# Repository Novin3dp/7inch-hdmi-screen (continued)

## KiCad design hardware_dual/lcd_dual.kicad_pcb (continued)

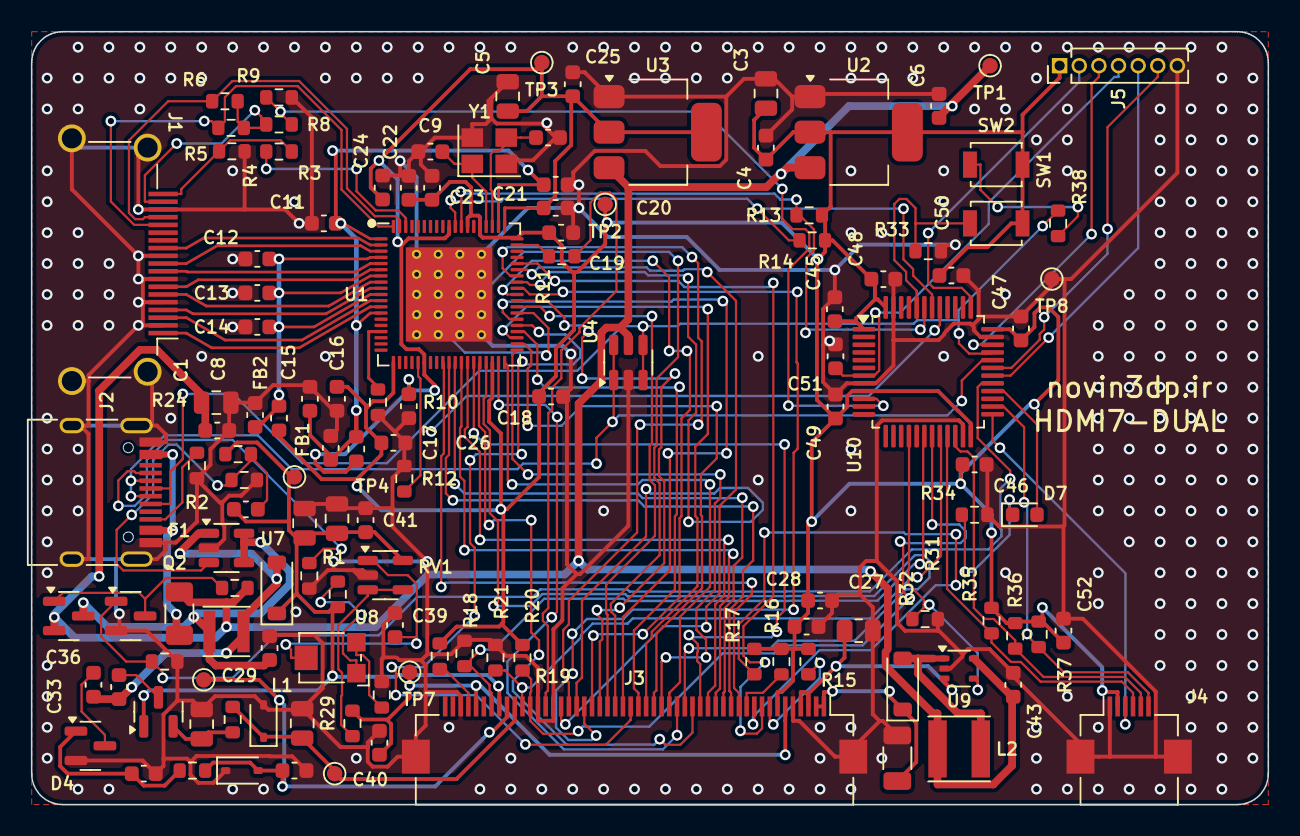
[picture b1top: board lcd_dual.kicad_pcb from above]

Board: 2 copper layers, 80.0 x 50.0 mm, 127 parts (0 on the bottom side), 99 nets.

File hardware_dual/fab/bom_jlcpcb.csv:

Comment,Designator,Footprint,MPN,LCSC Part #,Qty
BOOT (DFU),SW1,SW_SPST_B3U-1000P,Omron B3U-1000P,,1
BOOT CH32,SW2,SW_SPST_B3U-1000P,Omron B3U-1000P,,1
100nF,"C2,C4,C11,C12,C13,C14,C15,C16,C17,C18,C19,C20,C21,C22,C23,C24,C28,C39,C41,C45,C46,C47,C48,C49,C51",C_0603_1608Metric,,C14663,25
100nF 50V,"C33,C36",C_0603_1608Metric,,C14663,2
10pF,C30,C_0603_1608Metric,,,1
10uF,"C6,C7,C8,C25,C26,C29,C43",C_0603_1608Metric,,C19702,7
18pF,"C9,C10",C_0603_1608Metric,,,2
1uF,"C27,C40,C52",C_0603_1608Metric,,C15849,3
1uF 25V,"C37,C38",C_0603_1608Metric,,C15849,2
4.7uF,C50,C_0603_1608Metric,,,1
1uF 50V,C34,C_0805_2012Metric,,,1
22uF,"C1,C3,C5",C_0805_2012Metric,,,3
4.7uF 25V,"C31,C32,C35",C_0805_2012Metric,,,3
2.2uF 50V,C42,C_1206_3216Metric,,,1
Touch FPC 6P 0.5mm,J4,Hirose_FH12-6S-0.5SH_1x06-1MP_P0.50mm_Horizontal,Hirose FH12-6S-0.5SH (check contact side of your CTP),,1
HDMI-A receptacle,J1,HDMI_A_Amphenol_10029449-x01xLF_Horizontal,Amphenol 10029449-001RLF (or equivalent SMT HDMI-A),,1
USB-C (power + touch USB),J2,USB_C_Receptacle_HRO_TYPE-C-31-M-12,HRO TYPE-C-31-M-12,C165948,1
25MHz 12pF,Y1,Crystal_SMD_3225-4Pin_3.2x2.5mm,X322525MOB4SI (25MHz CL=12pF),,1
MBR0530,D1,D_SOD-123,MBR0530T1G,,1
MBR0560,D6,D_SOD-123,MBR0560T1G,,1
16V 2%,D3,D_SOD-323,BZX384-B16,,1
6.8V 2%,D5,D_SOD-323,BZX384-B6V8,,1
PTC 1.1A hold,F1,Fuse_1206_3216Metric,1206L110/16 (or BSMD1206-110),,1
600R@100MHz,"FB1,FB2",L_0603_1608Metric,BLM18PG601SN1D,,2
10uH 0.6A,L1,L_Taiyo-Yuden_NR-30xx,NR3015T100M,,1
10uH 1.2A,L2,L_Taiyo-Yuden_NR-40xx,NR4018T100M,,1
green,D7,LED_0603_1608Metric,,,1
STM32F072CBT6 / CH32X035C8T6,U10,LQFP-48_7x7mm_P0.5mm,"STM32F072CBT6 (or CH32X035C8T6, same footprint)",,1
AMS1117-1.8,U3,SOT-223-3_TabPin2,AMS1117-1.8,,1
AMS1117-3.3,U2,SOT-223-3_TabPin2,AMS1117-3.3,C6186,1
2N7002,Q2,SOT-23,2N7002,C8545,1
AO3401A,Q1,SOT-23,AO3401A,C15127,1
BAT54S,"D2,D4",SOT-23,BAT54S,,2
LM321,U8,SOT-23-5,LM321MFX,,1
TPS61040,U7,SOT-23-5,TPS61040DBVR,,1
USBLC6-2SC6,U4,SOT-23-6,USBLC6-2SC6,C7519,1
TPS61169DCKR,U9,SOT-353_SC-70-5,TPS61169DCKR,,1
10k trim (VCOM),RV1,Potentiometer_Bourns_TC33X_Vertical,Bourns TC33X-2-103E,,1
100k,"R4,R22,R23,R32",R_0603_1608Metric,,C25803,4
100k 1%,R25,R_0603_1608Metric,,C25803,1
10k,"R12,R15,R16,R17,R18,R19,R20,R21,R33,R37",R_0603_1608Metric,,C25804,10
13k 1%,R29,R_0603_1608Metric,,,1
1k,"R3,R34",R_0603_1608Metric,,C21190,2
2.2k,"R26,R27,R35,R36",R_0603_1608Metric,,,4
22R,R11,R_0603_1608Metric,,,1
22k,R8,R_0603_1608Metric,,,1
2k 1%,R10,R_0603_1608Metric,,,1
30k 1%,R28,R_0603_1608Metric,,,1
33R,R30,R_0603_1608Metric,,,1
33k,R9,R_0603_1608Metric,,,1
4.7k,"R13,R14,R38",R_0603_1608Metric,,C23162,3
47k,"R5,R6",R_0603_1608Metric,,,2
5.1k,"R1,R2",R_0603_1608Metric,,C23186,2
750k 1%,R24,R_0603_1608Metric,,,1
1.13R 1%,R31,R_0805_2012Metric,,,1
"AT070TN92 FPC (0.5mm 50P, top contact)",J3,FPC_50P_P0.5_TopContact_AT070TN92,Hirose FH12A-50S-0.5SH(55) (top contact),,1
LT8619C,U1,Lontium_QFN-76_9x9mm_P0.4mm_EP5.81x6.31mm,LT8619C (Lontium),,1

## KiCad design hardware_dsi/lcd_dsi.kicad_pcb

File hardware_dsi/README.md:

# نسخه‌ی DSI: راه‌اندازی AT070TN92 مستقیم از پورت DSI رزبری‌پای

این برد دولایه (۶۸×۴۲ میلی‌متر) همان پنل ۷ اینچ AT070TN92 و تاچ GT915 را این بار از **پورت DSI رزبری‌پای** راه می‌اندازد. نسخه‌ی HDMI در پوشه‌ی `hardware/` دست‌نخورده باقی مانده است.

* **DSI رزبری‌پای** (۲ لِین) ← **ICN6211** (مبدل MIPI-DSI به RGB888) ← کانکتور FPC پنجاه‌پین پنل
* **تاچ GT915** مستقیم روی **I2C کانکتور DSI**؛ درایور `goodix` لینوکس آن را می‌خواند. میکروکنترلر و USB حذف شده‌اند.
* **۵ ولت و ۴ سیگنال کنترلی** با یک کابل ۸ رشته از هدر ۴۰ پین رزبری‌پای می‌آیند (کابل DSI تغذیه‌ی ۵ ولت ندارد).
* بخش تغذیه‌ی پنل (AVDD، VGH، VGL، VCOM) و درایور بک‌لایت همان مدارهای نسخه‌ی HDMI هستند.

> ⚠️ این طراحی همه‌ی بررسی‌های نرم‌افزاری را پاس کرده: DRC، تطبیق شماتیک با PCB و کامپایل Overlay. ولی **هنوز ساخته و روی سخت‌افزار تست نشده است**. بخش «ریسک‌ها» را حتماً بخوانید.

---

## ۱) بلوک دیاگرام

```
 Pi DSI (15P 1mm) ──D0,D1,CLK──► ICN6211 ──RGB888 + DE + PCLK──► J3 (FPC 50P) ──► AT070TN92
        │ SDA/SCL (i2c_csi_dsi)                                     ▲ AVDD/VGH/VGL/VCOM, VLED
        └──────────────────────────► J4 (FPC 6P) ──► تاچ GT915      │
 Pi 40-pin ──J2──► 5V ─► PTC ─► AMS1117-3.3 ─► 3.3V (ICN6211، منطق پنل، تاچ)
                  DSI_EN (GPIO22) ─► EN آی‌سی، RESET پنل (۱ms)، BIAS_EN (RC حدود ۵۰ms) ─► TPS61040 + پمپ‌های بار + LM321
                  TP_INT (GPIO27)، TP_RST (GPIO17) ─► تاچ
                  BL_PWM (GPIO18) ─► TPS61165 (بک‌لایت ۱۸۰mA؛ پیش‌فرض روشن)
```

| بخش | قطعه | توضیح |
|---|---|---|
| مبدل DSI | ICN6211 (QFN48 6×6، LCSC C246085) | هر سه تغذیه 3.3V، کلاک مرجع از کلاک DSI (پایه REF_CLK به زمین)، VCORE با 1µF + 10nF |
| بایاس پنل | TPS61040 + 2×BAT54S + زنر | AVDD 10.4V، VGH 16V، VGL −6.8V |
| VCOM | LM321 + تریمر RV1 | 2.55 تا 4.5 ولت |
| بک‌لایت | TPS61165 | 182mA، روشن/خاموش یا PWM از GPIO18 |
| تغذیه | AMS1117-3.3 | از 5V هدر |

**ترتیب روشن شدن کاملاً سخت‌افزاری است.** وقتی لینوکس پایه‌ی EN پل را بالا می‌برد، RESET پنل بعد از حدود ۱ms آزاد می‌شود. بعد از حدود ۵۰ms هم تغذیه‌های AVDD، VGL و VGH روشن می‌شوند. با خاموش شدن نمایشگر (EN پایین) همه‌ی این‌ها با هم خاموش می‌شوند.

---

## ۲) اتصال به رزبری‌پای

### کابل DSI (J1)

* J1 یک کانکتور FPC پانزده‌پین با گام 1mm است، با همان پین‌اوت کانکتور DSI در Pi 3 و Pi 4.
* **Pi 5 و CM4/CM5** کانکتور ۲۲ پین 0.5mm دارند. برای آن‌ها از کابل استاندارد «Raspberry Pi Display Cable 22-pin to 15-pin» استفاده کنید.
* **جهت کابل:** برای J1 یک کانکتور **Dual-contact** (کنتاکت در بالا و پایین) بگذارید. اگر تصویر نیامد، کابل را در سمت برد **برعکس** (رو به پایین) جا بزنید؛ این کار ترتیب پین‌ها را آینه می‌کند.
* پایه‌های ۱، ۱۴ و ۱۵ کانکتور روی برد عمداً **وصل نیستند**: پین ۱ زمین است و ۱۴ و ۱۵ تغذیه‌ی 3.3V رزبری‌پای. برای همین اگر کابل برعکس جا خورد، 3.3V رزبری‌پای به زمین اتصال کوتاه نمی‌شود. زمین از پایه‌های ۴، ۷، ۱۰ و ۱۳ وصل است.

### کابل هدر (J2، هدر ۸ پین 2.54mm)

| J2 | سیگنال | پین هدر رزبری‌پای |
|---|---|---|
| 1 | +5V | 2 |
| 2 | +5V | 4 |
| 3 | GND | 6 |
| 4 | GND | 9 |
| 5 | DSI_EN (EN آی‌سی ICN6211) | 15 (GPIO22) |
| 6 | TP_INT | 13 (GPIO27) |
| 7 | TP_RST | 11 (GPIO17) |
| 8 | BL_PWM (بک‌لایت) | 12 (GPIO18) |

اگر GPIO دیگری لازم دارید، پارامترهای Overlay را عوض کنید (بخش ۳). بدون سیم BL_PWM بک‌لایت همیشه روشن است (مقاومت pull-up 10k).

### تاچ (J4)

ترتیب پین‌ها مثل نسخه‌ی HDMI است: `1 GND, 2 3.3V, 3 INT, 4 SCL, 5 SDA, 6 RST`. خطوط SCL و SDA به I2C کانکتور DSI وصل‌اند. **ترتیب پین FPC تاچ‌پنل خودتان را چک کنید.**

### مصرف

بک‌لایت حدود 2W، پنل و ICN6211 حدود 0.4W: در مجموع **حدود 0.5A از 5V هدر**. منبع تغذیه‌ی رزبری‌پای باید این جریان اضافه را بدهد (منبع رسمی 3A/5A کافی است).

---

## ۳) نرم‌افزار رزبری‌پای

درایور لینوکس ICN6211 (`chipone-icn6211`) در کرنل اصلی لینوکس هست، **ولی در کرنل Raspberry Pi OS فعال نشده**. اسکریپت `rpi_dsi/icn6211/install.sh` سورس همان نسخه‌ی کرنل را از گیت‌هاب Raspberry Pi دانلود می‌کند. بعد ماژول را می‌سازد و نصب می‌کند، Overlay را کامپایل می‌کند و خط لازم را به `config.txt` اضافه می‌کند:

```sh
sudo apt install linux-headers-rpi-v8 device-tree-compiler   # Pi 5: linux-headers-rpi-2712
cd rpi_dsi/icn6211
sudo ./install.sh
sudo reboot
```

بعد از هر به‌روزرسانی کرنل، `install.sh` را دوباره اجرا کنید.

فایل `rpi_dsi/at070tn92-dsi-overlay.dts` این‌ها را تعریف می‌کند:
* پل `chipone,icn6211` روی DSI1 با ۲ لِین و EN روی GPIO22
* پنل `panel-dpi` با تایمینگ دیتاشیت AT070TN92: 33.3MHz، HFP 210، HBP+HS 46، VFP 22، VBP+VS 23. حالت DE فعال است و داده در لبه‌ی بالارونده‌ی کلاک فرستاده می‌شود، چون پنل در لبه‌ی پایین‌رونده نمونه می‌گیرد.
* بک‌لایت `gpio-backlight` روی GPIO18
* تاچ `goodix` با آدرس 0x5D روی `i2c_csi_dsi`، INT روی GPIO27 و RST روی GPIO17

پارامترهای Overlay (در `config.txt`، مثلاً `dtoverlay=at070tn92-dsi,touch_invx,touch_invy`):

| پارامتر | کار |
|---|---|
| `dsi0` | استفاده از پورت DSI0 (روی Pi 5: DISP0؛ روی CM: DSI0) |
| `enable_gpio=N` / `backlight_gpio=N` / `touch_int=N` / `touch_reset=N` | تغییر GPIOها |
| `touch_invx` / `touch_invy` / `touch_swapxy` | اصلاح جهت تاچ |
| `touch_addr=0x14` / `disable_touch` | آدرس دیگر تاچ / غیرفعال کردن تاچ |
| `clock-frequency=N` | فرکانس پیکسل (پیش‌فرض 33300000) |

چرخش ۱۸۰ درجه: در دسکتاپ از Screen Configuration، یا با سخت‌افزار: R19/R20 (پایه‌های L/R و U/D پنل) را برعکس ببندید و تاچ را با `touch_invx,touch_invy` برگردانید.

---

## ۴) مشخصات PCB

| مورد | مقدار |
|---|---|
| ابعاد | 68 × 42 mm، گوشه‌های گرد R2 (نسخه‌ی HDMI: 80×50) |
| لایه | ۲ لایه، FR4، مس 1oz |
| حداقل ترک/فاصله | 0.15 / 0.15 mm؛ ویا 0.3/0.6 mm (ظرفیت استاندارد JLCPCB) |
| قطعات | ۸۵ قطعه، **فقط روی رو (Top)** |
| زوج‌های DSI | دستی کشیده شده‌اند (حدود ۸ میلی‌متر، ترک 0.2mm). ترتیب لِین‌ها در کانکتور رزبری‌پای و ICN6211 یکی نیست، برای همین زوج کلاک برای عبور از زیر لِین ۱ از لایه‌ی پشت می‌رود (۴ ویا). |
| گذرگاه RGB | ۲۶ خط RGB/DE/DCLK دستی و منظم کشیده شده‌اند: هر خط ستون خودش را دارد و با زاویه‌ی ۳۰ درجه به پد FPC می‌رسد. فقط DE از زیر گذرگاه روی لایه‌ی پشت رد می‌شود. بقیه‌ی نت‌ها با Freerouting کشیده شده‌اند. |
| DRC | **۰ خطا و ۰ اتصال باز**؛ ۸۲ برچسب سیلک بدون تداخل، ۳ برچسب (C40، D3، R18) فقط در نقشه‌ی مونتاژ `docs/img/dsi_pcb_assembly.png` آمده‌اند |

---

## ۵) ساخت (JLCPCB)

1. `hardware_dsi/fab/lcd_dsi_gerbers.zip` برای ساخت PCB.
2. `hardware_dsi/fab/bom_jlcpcb.csv` و `cpl_jlcpcb.csv` برای مونتاژ. شماره‌ی LCSC آی‌سی ICN6211: C246085 (موجودی را هنگام سفارش چک کنید).
3. نقاط تست TP1..TP7 نصب نمی‌شوند. J2 (هدر) را خودتان لحیم کنید.

---

## ۶) ریسک‌ها و نکات (لطفاً بخوانید)

1. **ترتیب رنگ‌ها:** درایور لینوکس رجیستر جابه‌جایی RGB را تنظیم نمی‌کند. طبق راهنمای Chipone فرض شده که حالت پیش‌فرض `DATA[7:0]=R`، `DATA[15:8]=G` و `DATA[23:16]=B` است. اگر قرمز و آبی جابه‌جا بودند، ایراد از این فرض است. می‌توان آن را با یک خط در درایور (رجیستر SYS_CTRL) اصلاح کرد.
2. **جهت کابل DSI** (بخش ۲): کانکتور Dual-contact بگذارید و اگر تصویر نیامد کابل را در سمت برد برعکس کنید.
3. امپدانس زوج‌های DSI روی برد ۲ لایه دقیقاً 100Ω نیست. ولی مسیرها کوتاه‌اند (حدود ۸mm) و سرعت هر لِین برای 800×480 فقط حدود 400Mbps است. ضخامت 1.0mm برای برد بهتر است.
4. پل I2C کانکتور DSI به pull-up نیاز دارد؛ R2/R3 (4.7k به 3.3V برد) روی برد هستند. برد را قبل یا هم‌زمان با رزبری‌پای روشن کنید (هر دو از یک 5V تغذیه می‌شوند).
5. درایور goodix شناسه‌ی GT915 را از خود آی‌سی می‌خواند. Config تاچ‌پنل در فلش GT915 است. اگر محورها برعکس بود از پارامترهای `touch_*` استفاده کنید.
6. VCOM هر پنل را با RV1 برای کمترین فلیکر تنظیم کنید (نقطه‌ی تست TP6).
7. جهت FPC پنل و کانکتور Top-contact مثل نسخه‌ی HDMI است (بخش ۴ README اصلی).

---

## ۷) ساخت دوباره از اسکریپت‌ها

اسکریپت‌های عمومی (`sexpr`، `symlib`، `silk`) از `hardware/gen` استفاده می‌شوند؛ بقیه در `hardware_dsi/gen` هستند و منبع اصلی طراحی فایل `design.py` است.

```sh
cd hardware_dsi/gen
python3 make_libs.py && python3 gen_sch.py && python3 verify_netlist.py
python3.12 pcb.py                         # چیدمان + زوج‌های DSI + خروجی‌های کوتاه پایه‌های ICN6211
python3.12 route.py export
java -jar freerouting-2.0.1.jar --gui.enabled=false -de ../lcd_dsi.dsn -do ../lcd_dsi.ses -mp 100 --router.via_costs=30
python3.12 route.py import ../lcd_dsi.ses
python3.12 check.py --fill
python3 fab.py
```

فایل `lcd_dsi.ses` (مسیرهای برد فعلی) در ریپازیتوری هست.

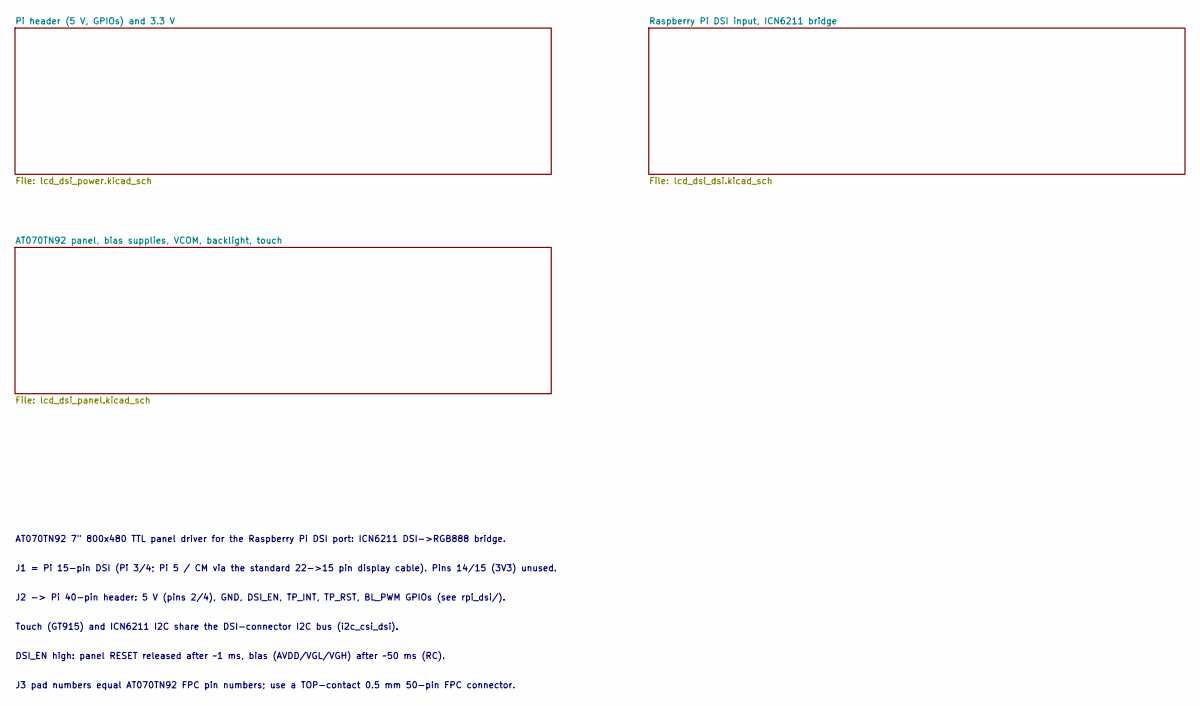
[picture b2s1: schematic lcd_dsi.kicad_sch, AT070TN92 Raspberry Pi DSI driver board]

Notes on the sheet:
AT070TN92 7" 800x480 TTL panel driver for the Raspberry Pi DSI port: ICN6211 DSI->RGB888 bridge.
J1 = Pi 15-pin DSI (Pi 3/4; Pi 5 / CM via the standard 22->15 pin display cable). Pins 14/15 (3V3) unused.
J2 -> Pi 40-pin header: 5 V (pins 2/4), GND, DSI_EN, TP_INT, TP_RST, BL_PWM GPIOs (see rpi_dsi/).
Touch (GT915) and ICN6211 I2C share the DSI-connector I2C bus (i2c_csi_dsi).
DSI_EN high: panel RESET released after ~1 ms, bias (AVDD/VGL/VGH) after ~50 ms (RC).
J3 pad numbers equal AT070TN92 FPC pin numbers; use a TOP-contact 0.5 mm 50-pin FPC connector.

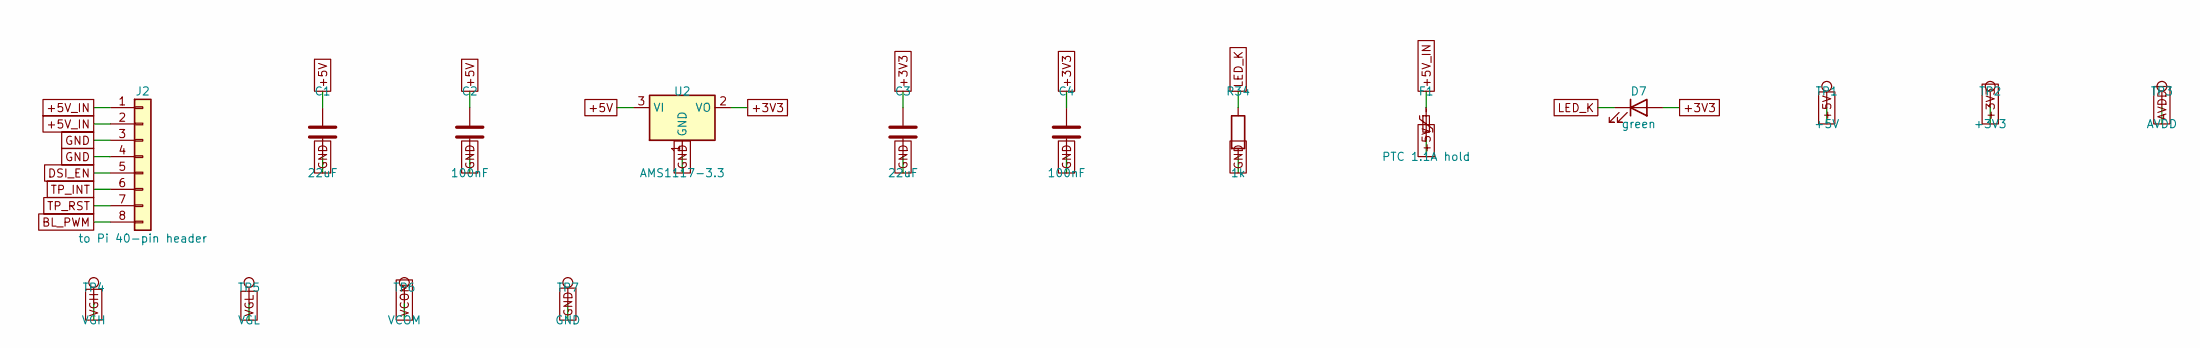
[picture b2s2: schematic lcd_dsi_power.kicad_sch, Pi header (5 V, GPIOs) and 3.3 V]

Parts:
C1, C3: 22uF; C_0805_2012Metric
C2, C4: 100nF; C_0603_1608Metric; LCSC C14663
D7: green; LED_0603_1608Metric
F1: PTC 1.1A hold; Fuse_1206_3216Metric; MPN 1206L110/16 (or BSMD1206-110)
J2: to Pi 40-pin header; PinHeader_1x08_P2.54mm_Vertical; MPN 1x8 2.54mm pin header
R34: 1k; R_0603_1608Metric; LCSC C21190
TP1: +5V; TestPoint_Pad_D1.0mm
TP2: +3V3; TestPoint_Pad_D1.0mm
TP3: AVDD; TestPoint_Pad_D1.0mm
TP4: VGH; TestPoint_Pad_D1.0mm
TP5: VGL; TestPoint_Pad_D1.0mm
TP6: VCOM; TestPoint_Pad_D1.0mm
TP7: GND; TestPoint_Pad_D1.0mm
U2: AMS1117-3.3; SOT-223-3_TabPin2; MPN AMS1117-3.3; LCSC C6186

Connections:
+3V3: C3.1, C4.1, D7.2 (A), TP2.1, U2.2 (VO); also elsewhere on the board
+5V: C1.1, C2.1, F1.2, TP1.1, U2.3 (VI); also elsewhere on the board
+5V_IN: F1.1, J2.1, J2.2
AVDD: TP3.1; also elsewhere on the board
BL_PWM: J2.8; also elsewhere on the board
DSI_EN: J2.5; also elsewhere on the board
GND: C1.2, C2.2, C3.2, C4.2, J2.3, J2.4, R34.2, TP7.1, U2.1 (GND); also elsewhere on the board
LED_K: D7.1 (K), R34.1
TP_INT: J2.6; also elsewhere on the board
TP_RST: J2.7; also elsewhere on the board
VCOM: TP6.1; also elsewhere on the board
VGH: TP4.1; also elsewhere on the board
VGL: TP5.1; also elsewhere on the board

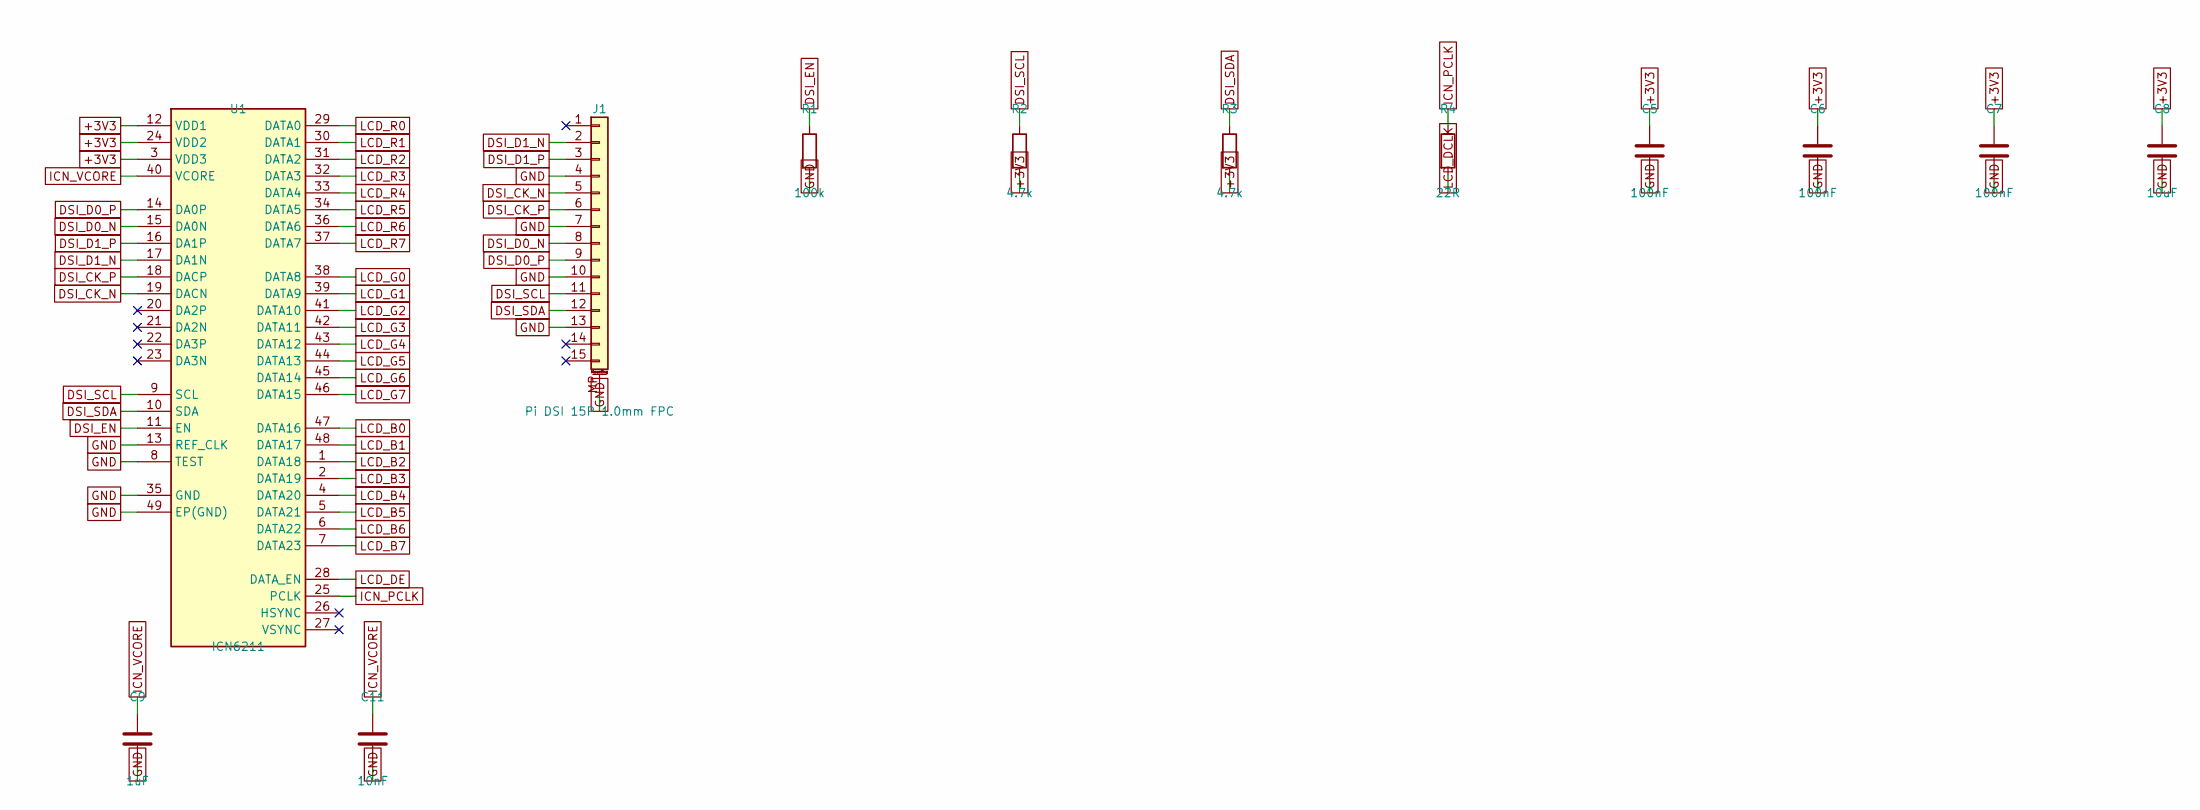
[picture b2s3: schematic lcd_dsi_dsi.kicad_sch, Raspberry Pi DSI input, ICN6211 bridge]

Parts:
C5, C6, C7: 100nF; C_0603_1608Metric; LCSC C14663
C8: 10uF; C_0603_1608Metric; LCSC C19702
C9: 1uF; C_0603_1608Metric; LCSC C15849
C11: 10nF; C_0603_1608Metric
J1: Pi DSI 15P 1.0mm FPC; FPC_15P_P1.0_PiDSI; MPN 1.0mm 15P FPC, dual contact (TE 1-84953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
R1: 100k; R_0603_1608Metric; LCSC C25803
R2, R3: 4.7k; R_0603_1608Metric; LCSC C23162
R4: 22R; R_0603_1608Metric
U1: ICN6211; QFN-48-1EP_6x6mm_P0.4mm_EP4.2x4.2mm_Vias0.3; MPN ICN6211 (Chipone); LCSC C246085

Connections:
+3V3: C5.1, C6.1, C7.1, C8.1, R2.2, R3.2, U1.3 (VDD3), U1.12 (VDD1), U1.24 (VDD2); also elsewhere on the board
DSI_CK_N: J1.5, U1.19 (DACN)
DSI_CK_P: J1.6, U1.18 (DACP)
DSI_D0_N: J1.8, U1.15 (DA0N)
DSI_D0_P: J1.9, U1.14 (DA0P)
DSI_D1_N: J1.2, U1.17 (DA1N)
DSI_D1_P: J1.3, U1.16 (DA1P)
DSI_EN: R1.1, U1.11 (EN); also elsewhere on the board
DSI_SCL: J1.11, R2.1, U1.9 (SCL); also elsewhere on the board
DSI_SDA: J1.12, R3.1, U1.10 (SDA); also elsewhere on the board
GND: C5.2, C6.2, C7.2, C8.2, C9.2, C11.2, J1.4, J1.7, J1.10, J1.13, J1.MP (MountPin), R1.2, U1.8 (TEST), U1.13 (REF_CLK), U1.35 (GND), U1.49 (EP(GND)); also elsewhere on the board
ICN_PCLK: R4.1, U1.25 (PCLK)
ICN_VCORE: C9.1, C11.1, U1.40 (VCORE)
LCD_B0: U1.47 (DATA16); also elsewhere on the board
LCD_B1: U1.48 (DATA17); also elsewhere on the board
LCD_B2: U1.1 (DATA18); also elsewhere on the board
LCD_B3: U1.2 (DATA19); also elsewhere on the board
LCD_B4: U1.4 (DATA20); also elsewhere on the board
LCD_B5: U1.5 (DATA21); also elsewhere on the board
LCD_B6: U1.6 (DATA22); also elsewhere on the board
LCD_B7: U1.7 (DATA23); also elsewhere on the board
LCD_DCLK: R4.2; also elsewhere on the board
LCD_DE: U1.28 (DATA_EN); also elsewhere on the board
LCD_G0: U1.38 (DATA8); also elsewhere on the board
LCD_G1: U1.39 (DATA9); also elsewhere on the board
LCD_G2: U1.41 (DATA10); also elsewhere on the board
LCD_G3: U1.42 (DATA11); also elsewhere on the board
LCD_G4: U1.43 (DATA12); also elsewhere on the board
LCD_G5: U1.44 (DATA13); also elsewhere on the board
LCD_G6: U1.45 (DATA14); also elsewhere on the board
LCD_G7: U1.46 (DATA15); also elsewhere on the board
LCD_R0: U1.29 (DATA0); also elsewhere on the board
LCD_R1: U1.30 (DATA1); also elsewhere on the board
LCD_R2: U1.31 (DATA2); also elsewhere on the board
LCD_R3: U1.32 (DATA3); also elsewhere on the board
LCD_R4: U1.33 (DATA4); also elsewhere on the board
LCD_R5: U1.34 (DATA5); also elsewhere on the board
LCD_R6: U1.36 (DATA6); also elsewhere on the board
LCD_R7: U1.37 (DATA7); also elsewhere on the board

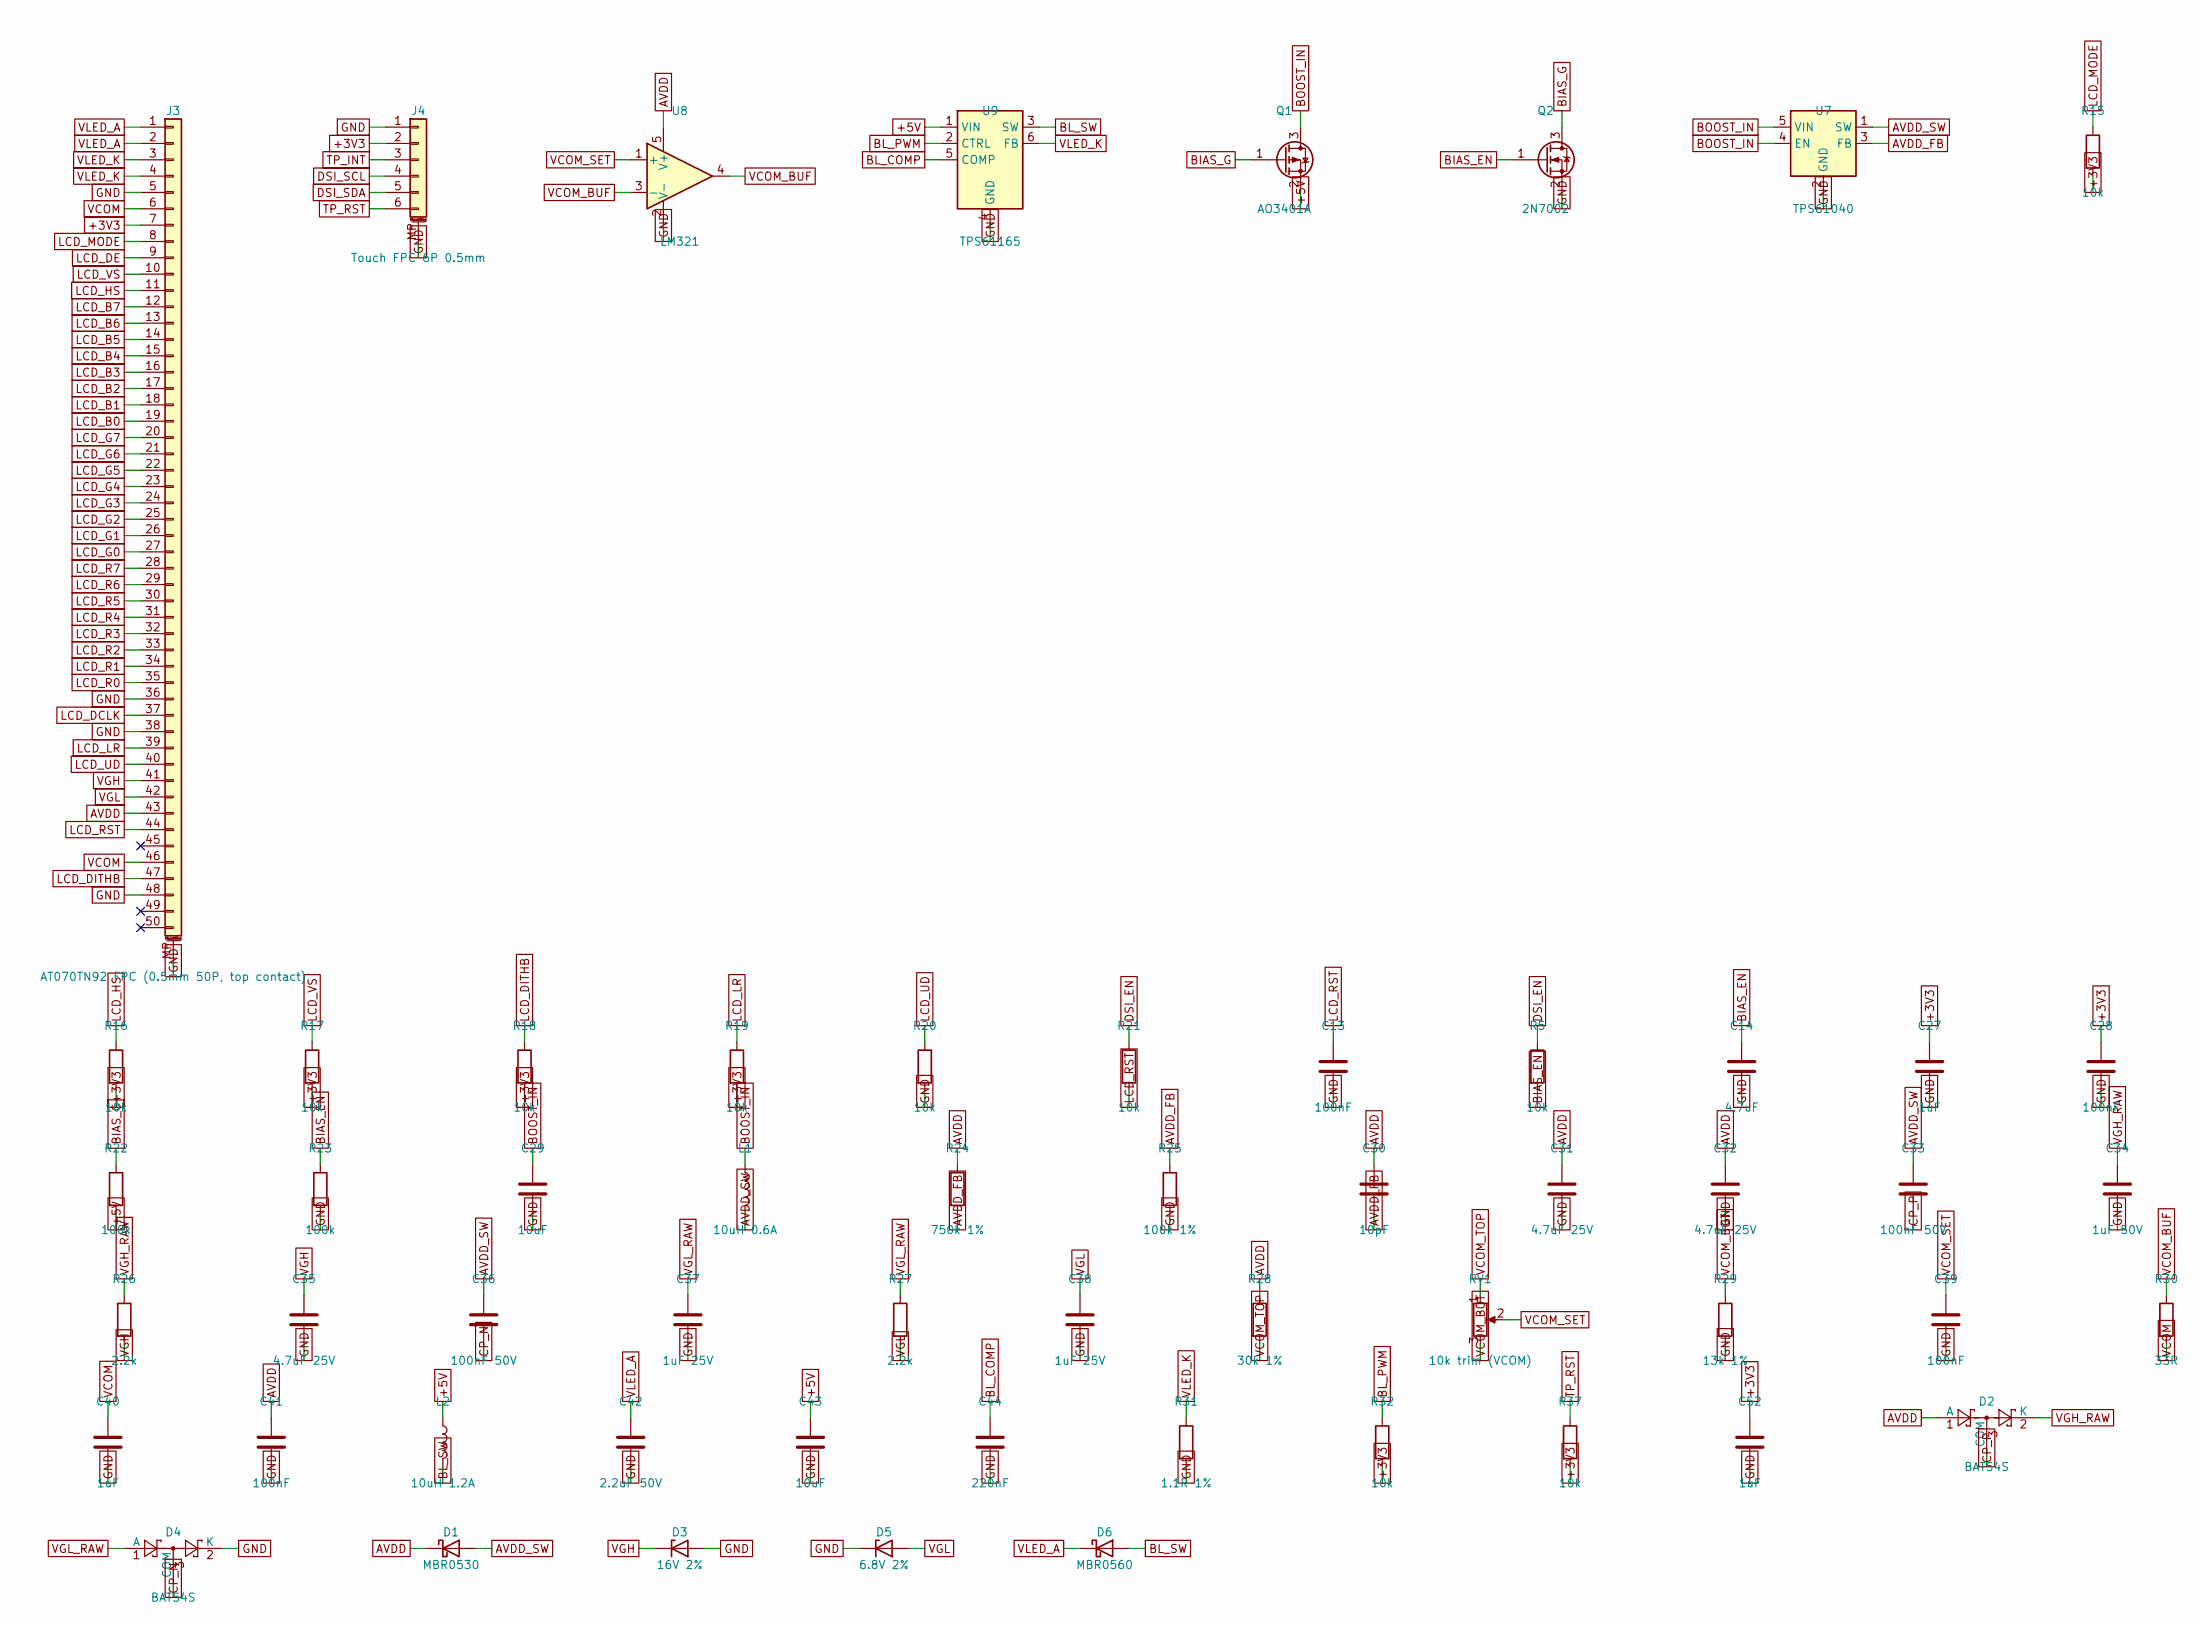
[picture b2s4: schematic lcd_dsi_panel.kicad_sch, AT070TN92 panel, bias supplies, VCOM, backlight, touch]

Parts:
C13, C28, C39, C41: 100nF; C_0603_1608Metric; LCSC C14663
C14: 4.7uF; C_0603_1608Metric
C27, C40, C52: 1uF; C_0603_1608Metric; LCSC C15849
C29, C43: 10uF; C_0603_1608Metric; LCSC C19702
C30: 10pF; C_0603_1608Metric
C31, C32, C35: 4.7uF 25V; C_0805_2012Metric
C33, C36: 100nF 50V; C_0603_1608Metric; LCSC C14663
C34: 1uF 50V; C_0805_2012Metric
C37, C38: 1uF 25V; C_0603_1608Metric; LCSC C15849
C42: 2.2uF 50V; C_1206_3216Metric
C44: 220nF; C_0603_1608Metric
D1: MBR0530; D_SOD-123; MPN MBR0530T1G
D2, D4: BAT54S; SOT-23; MPN BAT54S
D3: 16V 2%; D_SOD-323; MPN BZX384-B16
D5: 6.8V 2%; D_SOD-323; MPN BZX384-B6V8
D6: MBR0560; D_SOD-123; MPN MBR0560T1G
J3: AT070TN92 FPC (0.5mm 50P, top contact); FPC_50P_P0.5_TopContact_AT070TN92; MPN Hirose FH12A-50S-0.5SH(55) (top contact)
J4: Touch FPC 6P 0.5mm; Hirose_FH12-6S-0.5SH_1x06-1MP_P0.50mm_Horizontal; MPN Hirose FH12-6S-0.5SH (check contact sid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
L1: 10uH 0.6A; L_Taiyo-Yuden_NR-30xx; MPN NR3015T100M
L2: 10uH 1.2A; L_Taiyo-Yuden_NR-40xx; MPN NR4018T100M
Q1: AO3401A; SOT-23; MPN AO3401A; LCSC C15127
Q2: 2N7002; SOT-23; MPN 2N7002; LCSC C8545
R5, R15, R16, R17, R18, R19, R20, R21, R32, R37: 10k; R_0603_1608Metric; LCSC C25804
R22, R23: 100k; R_0603_1608Metric; LCSC C25803
R24: 750k 1%; R_0603_1608Metric
R25: 100k 1%; R_0603_1608Metric; LCSC C25803
R26, R27: 2.2k; R_0603_1608Metric
R28: 30k 1%; R_0603_1608Metric
R29: 13k 1%; R_0603_1608Metric
R30: 33R; R_0603_1608Metric
R31: 1.1R 1%; R_0805_2012Metric
RV1: 10k trim (VCOM); Potentiometer_Bourns_TC33X_Vertical; MPN Bourns TC33X-2-103E
U7: TPS61040; SOT-23-5; MPN TPS61040DBVR
U8: LM321; SOT-23-5; MPN LM321MFX
U9: TPS61165; SOT-23-6; MPN TPS61165DBVR

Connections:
+3V3: C27.1, C28.1, C52.1, J3.7, J4.2, R15.2, R16.2, R17.2, R18.2, R19.2, R32.2, R37.2; also elsewhere on the board
+5V: C43.1, L2.1, Q1.2 (S), R22.2, U9.1 (VIN); also elsewhere on the board
AVDD: C30.1, C31.1, C32.1, C41.1, D1.1 (K), D2.1 (A), J3.43, R24.1, R28.1, U8.5 (V+); also elsewhere on the board
AVDD_FB: C30.2, R24.2, R25.1, U7.3 (FB)
AVDD_SW: C33.1, C36.1, D1.2 (A), L1.2, U7.1 (SW)
BIAS_EN: C14.1, Q2.1 (G), R5.2, R23.1
BIAS_G: Q1.1 (G), Q2.3 (D), R22.1
BL_COMP: C44.1, U9.5 (COMP)
BL_PWM: R32.1, U9.2 (CTRL); also elsewhere on the board
BL_SW: D6.2 (A), L2.2, U9.3 (SW)
BOOST_IN: C29.1, L1.1, Q1.3 (D), U7.4 (EN), U7.5 (VIN)
CP_N: C36.2, D4.3 (COM)
CP_P: C33.2, D2.3 (COM)
DSI_EN: R5.1, R21.1; also elsewhere on the board
DSI_SCL: J4.4; also elsewhere on the board
DSI_SDA: J4.5; also elsewhere on the board
GND: C13.2, C14.2, C27.2, C28.2, C29.2, C31.2, C32.2, C34.2, C35.2, C37.2, C38.2, C39.2, C40.2, C41.2, C42.2, C43.2, C44.2, C52.2, D3.2 (A), D4.2 (K), D5.1 (K), J3.5, J3.36, J3.38, J3.48, J3.MP (MountPin), J4.1, J4.MP (MountPin), Q2.2 (S), R20.2, R23.2, R25.2, R29.2, R31.2, U7.2 (GND), U8.2 (V-), U9.4 (GND); also elsewhere on the board
LCD_B0: J3.19; also elsewhere on the board
LCD_B1: J3.18; also elsewhere on the board
LCD_B2: J3.17; also elsewhere on the board
LCD_B3: J3.16; also elsewhere on the board
LCD_B4: J3.15; also elsewhere on the board
LCD_B5: J3.14; also elsewhere on the board
LCD_B6: J3.13; also elsewhere on the board
LCD_B7: J3.12; also elsewhere on the board
LCD_DCLK: J3.37; also elsewhere on the board
LCD_DE: J3.9; also elsewhere on the board
LCD_DITHB: J3.47, R18.1
LCD_G0: J3.27; also elsewhere on the board
LCD_G1: J3.26; also elsewhere on the board
LCD_G2: J3.25; also elsewhere on the board
LCD_G3: J3.24; also elsewhere on the board
LCD_G4: J3.23; also elsewhere on the board
LCD_G5: J3.22; also elsewhere on the board
LCD_G6: J3.21; also elsewhere on the board
LCD_G7: J3.20; also elsewhere on the board
LCD_HS: J3.11, R16.1
LCD_LR: J3.39, R19.1
LCD_MODE: J3.8, R15.1
LCD_R0: J3.35; also elsewhere on the board
LCD_R1: J3.34; also elsewhere on the board
LCD_R2: J3.33; also elsewhere on the board
LCD_R3: J3.32; also elsewhere on the board
LCD_R4: J3.31; also elsewhere on the board
LCD_R5: J3.30; also elsewhere on the board
LCD_R6: J3.29; also elsewhere on the board
LCD_R7: J3.28; also elsewhere on the board
LCD_RST: C13.1, J3.44, R21.2
LCD_UD: J3.40, R20.1
LCD_VS: J3.10, R17.1
TP_INT: J4.3; also elsewhere on the board
TP_RST: J4.6, R37.1; also elsewhere on the board
VCOM: C40.1, J3.6, J3.46, R30.2; also elsewhere on the board
VCOM_BOT: R29.1, RV1.3
VCOM_BUF: R30.1, U8.3 (-), U8.4
VCOM_SET: C39.1, RV1.2, U8.1 (+)
VCOM_TOP: R28.2, RV1.1
VGH: C35.1, D3.1 (K), J3.41, R26.2; also elsewhere on the board
VGH_RAW: C34.1, D2.2 (K), R26.1
VGL: C38.1, D5.2 (A), J3.42, R27.2; also elsewhere on the board
VGL_RAW: C37.1, D4.1 (A), R27.1
VLED_A: C42.1, D6.1 (K), J3.1, J3.2
VLED_K: J3.3, J3.4, R31.1, U9.6 (FB)

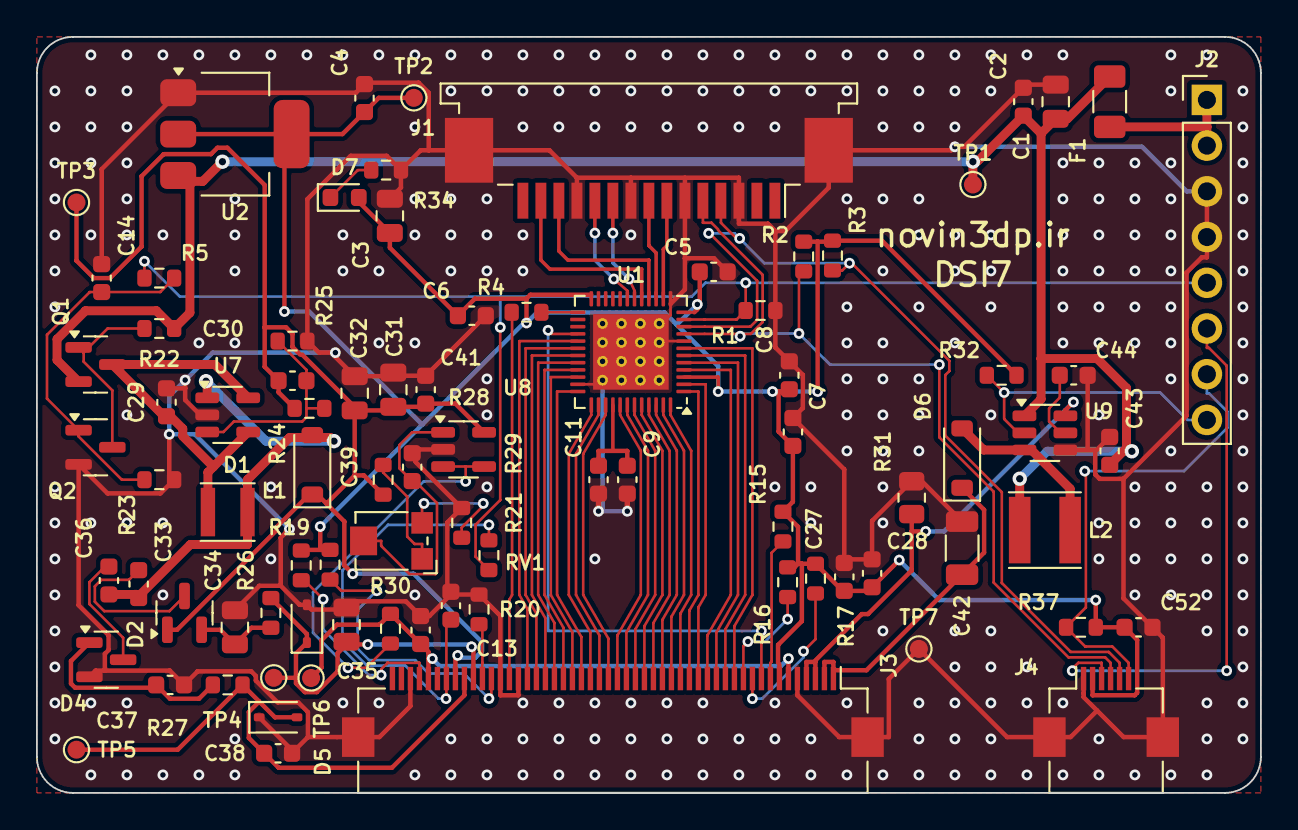
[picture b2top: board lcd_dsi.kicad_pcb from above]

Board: 2 copper layers, 68.0 x 42.0 mm, 85 parts (0 on the bottom side), 73 nets.

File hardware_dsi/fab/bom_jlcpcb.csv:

Comment,Designator,Footprint,MPN,LCSC Part #,Qty
100nF,"C2,C4,C5,C6,C7,C13,C28,C39,C41",C_0603_1608Metric,,C14663,9
100nF 50V,"C33,C36",C_0603_1608Metric,,C14663,2
10nF,C11,C_0603_1608Metric,,,1
10pF,C30,C_0603_1608Metric,,,1
10uF,"C8,C29,C43",C_0603_1608Metric,,C19702,3
1uF,"C9,C27,C40,C52",C_0603_1608Metric,,C15849,4
1uF 25V,"C37,C38",C_0603_1608Metric,,C15849,2
220nF,C44,C_0603_1608Metric,,,1
4.7uF,C14,C_0603_1608Metric,,,1
1uF 50V,C34,C_0805_2012Metric,,,1
22uF,"C1,C3",C_0805_2012Metric,,,2
4.7uF 25V,"C31,C32,C35",C_0805_2012Metric,,,3
2.2uF 50V,C42,C_1206_3216Metric,,,1
Touch FPC 6P 0.5mm,J4,Hirose_FH12-6S-0.5SH_1x06-1MP_P0.50mm_Horizontal,Hirose FH12-6S-0.5SH (check contact side of your CTP),,1
to Pi 40-pin header,J2,PinHeader_1x08_P2.54mm_Vertical,1x8 2.54mm pin header,,1
MBR0530,D1,D_SOD-123,MBR0530T1G,,1
MBR0560,D6,D_SOD-123,MBR0560T1G,,1
16V 2%,D3,D_SOD-323,BZX384-B16,,1
6.8V 2%,D5,D_SOD-323,BZX384-B6V8,,1
PTC 1.1A hold,F1,Fuse_1206_3216Metric,1206L110/16 (or BSMD1206-110),,1
10uH 0.6A,L1,L_Taiyo-Yuden_NR-30xx,NR3015T100M,,1
10uH 1.2A,L2,L_Taiyo-Yuden_NR-40xx,NR4018T100M,,1
green,D7,LED_0603_1608Metric,,,1
AMS1117-3.3,U2,SOT-223-3_TabPin2,AMS1117-3.3,C6186,1
2N7002,Q2,SOT-23,2N7002,C8545,1
AO3401A,Q1,SOT-23,AO3401A,C15127,1
BAT54S,"D2,D4",SOT-23,BAT54S,,2
LM321,U8,SOT-23-5,LM321MFX,,1
TPS61040,U7,SOT-23-5,TPS61040DBVR,,1
TPS61165,U9,SOT-23-6,TPS61165DBVR,,1
10k trim (VCOM),RV1,Potentiometer_Bourns_TC33X_Vertical,Bourns TC33X-2-103E,,1
100k,"R1,R22,R23",R_0603_1608Metric,,C25803,3
100k 1%,R25,R_0603_1608Metric,,C25803,1
10k,"R5,R15,R16,R17,R18,R19,R20,R21,R32,R37",R_0603_1608Metric,,C25804,10
13k 1%,R29,R_0603_1608Metric,,,1
1k,R34,R_0603_1608Metric,,C21190,1
2.2k,"R26,R27",R_0603_1608Metric,,,2
22R,R4,R_0603_1608Metric,,,1
30k 1%,R28,R_0603_1608Metric,,,1
33R,R30,R_0603_1608Metric,,,1
4.7k,"R2,R3",R_0603_1608Metric,,C23162,2
750k 1%,R24,R_0603_1608Metric,,,1
1.1R 1%,R31,R_0805_2012Metric,,,1
Pi DSI 15P 1.0mm FPC,J1,FPC_15P_P1.0_PiDSI,"1.0mm 15P FPC, dual contact (TE 1-84953-5 land pattern)",,1
"AT070TN92 FPC (0.5mm 50P, top contact)",J3,FPC_50P_P0.5_TopContact_AT070TN92,Hirose FH12A-50S-0.5SH(55) (top contact),,1
ICN6211,U1,QFN-48-1EP_6x6mm_P0.4mm_EP4.2x4.2mm_Vias0.3,ICN6211 (Chipone),C246085,1
